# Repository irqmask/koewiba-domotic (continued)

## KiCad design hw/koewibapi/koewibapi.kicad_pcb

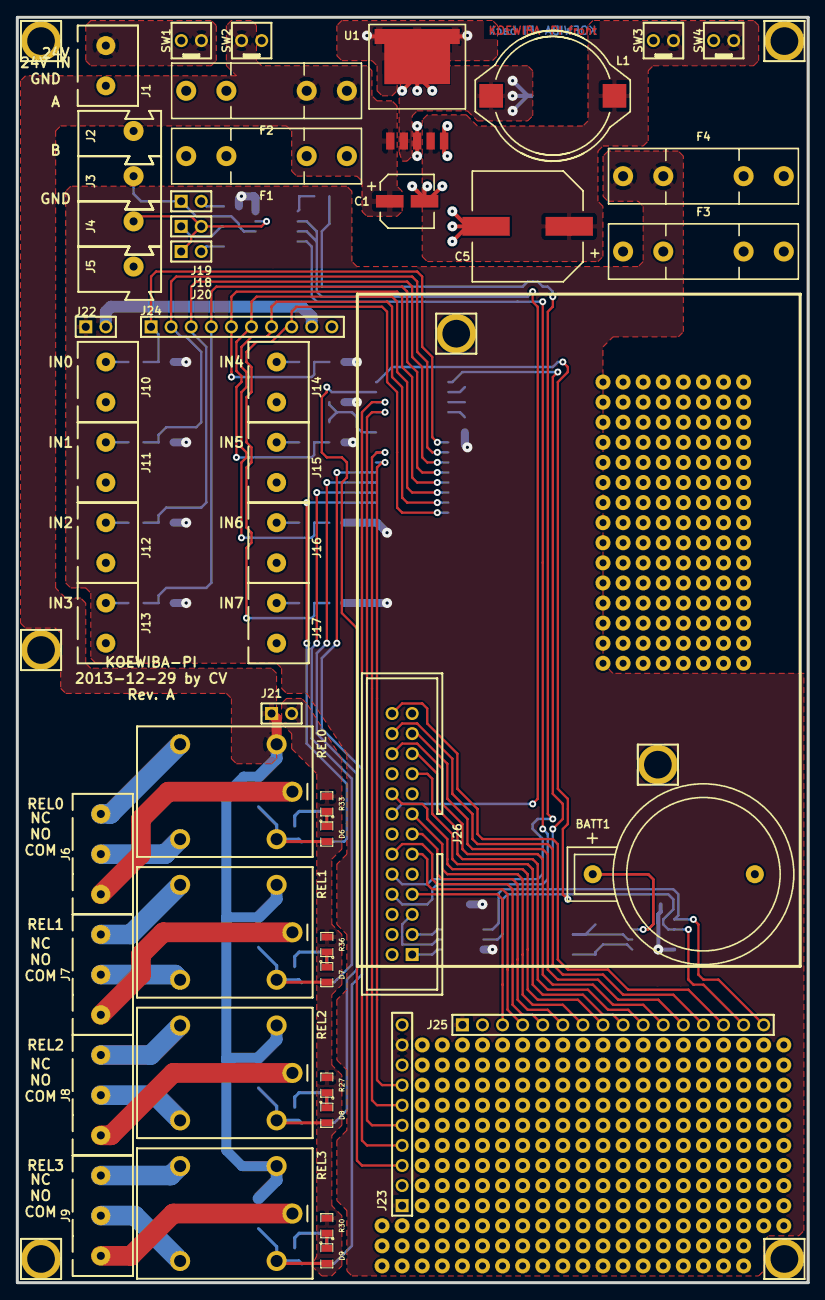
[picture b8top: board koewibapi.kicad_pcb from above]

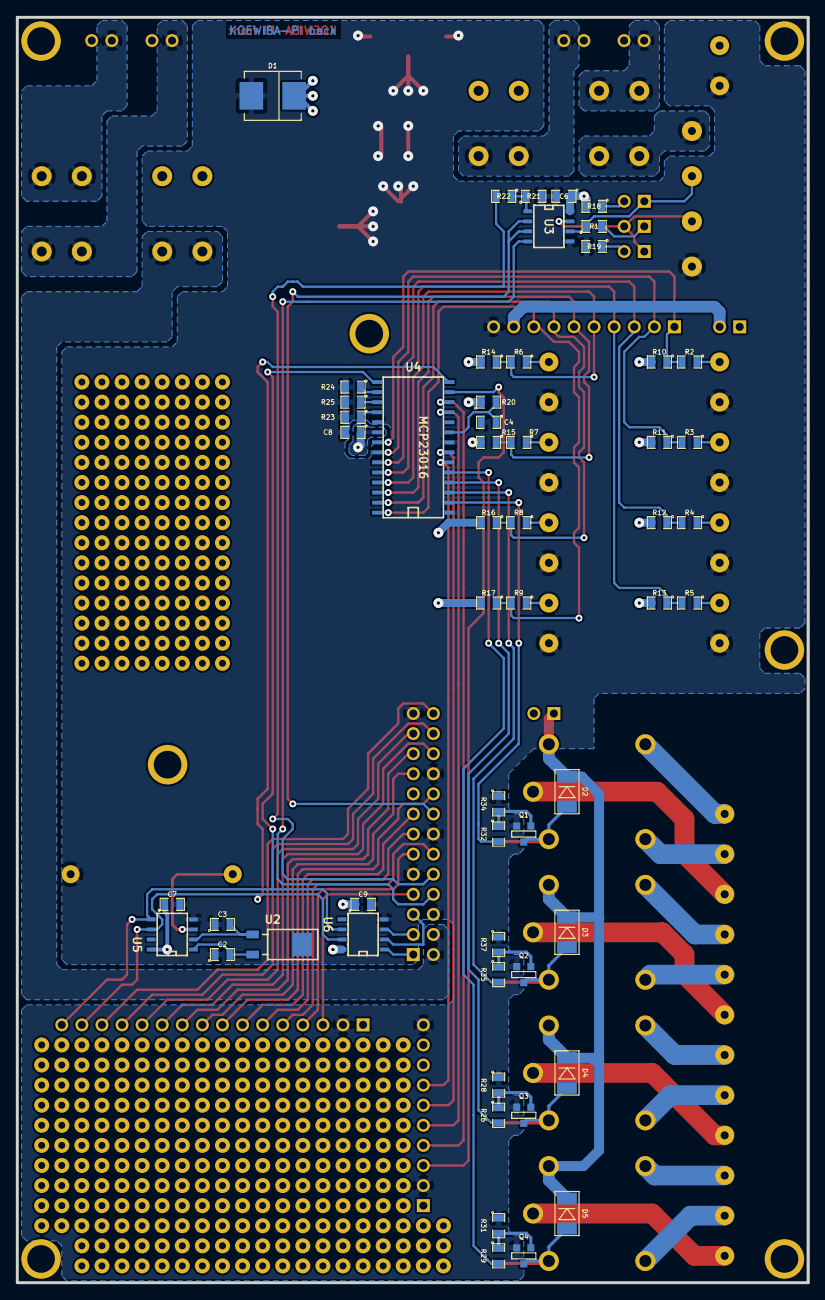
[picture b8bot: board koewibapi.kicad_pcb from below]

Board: 2 copper layers, 100.0 x 160.0 mm, 134 parts (54 on the bottom side), 96 nets.

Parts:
BATT1: 3V; CR2032H
C1: 100uF; cp_smd_6.3
C2, C3: 12.5pF; SM0805
C4: 33pF; SM0805
C5: 1000uF; cp_smd_12.5
C6, C7, C8, C9: 100nF; SM0805
D1: B_340_F; SMC
D2, D3, D4, D5: 1N4148; MINIMELF
D6, D7, D8, D9: LED_2,2V_25mA; SM0805
F1: 250V/1A_T; FUSE5-20
F2: 250V2,5A_T; FUSE5-20
F3: 250V/1,5A_T; FUSE5-20
F4: 250V/250mA_T; FUSE5-20
FIELD2x1, FIELD2x1#2, FIELD2x1#3, FIELD2x1#4, FIELD2x1#5: VAL**; FIELD2x1
FIELD5x2, FIELD5x2#2, FIELD5x2#3: VAL**; FIELD5x2
FIELD5x3, FIELD5x3#2, FIELD5x3#3: VAL**; FIELD5x3
FIELD5x4, FIELD5x4#2: VAL**; FIELD5x4
FIELD5x5, FIELD5x5#2, FIELD5x5#3, FIELD5x5#4, FIELD5x5#5, FIELD5x5#6, FIELD5x5#7, FIELD5x5#8, FIELD5x5#9: VAL**; FIELD5x5
H1, H2, H3, H4, H5, H6, H7: HOLE; HOLE_3.5mm
J1: POWER_IN_24V; CLAMP_5,08mm_2pole_stackable
J2: BUS_24V; WAGO243
J3, J4: CONN_1X1; WAGO243
J5: BUS_GND; WAGO243
J6: REL0; CLAMP_5,08mm_3pole_stackable
J7: REL1; CLAMP_5,08mm_3pole_stackable
J8: REL2; CLAMP_5,08mm_3pole_stackable
J9: REL3; CLAMP_5,08mm_3pole_stackable
J10: IN0; CLAMP_5,08mm_2pole_stackable
J11: IN1; CLAMP_5,08mm_2pole_stackable
J12: IN2; CLAMP_5,08mm_2pole_stackable
J13: IN3; CLAMP_5,08mm_2pole_stackable
J14: IN4; CLAMP_5,08mm_2pole_stackable
J15: IN5; CLAMP_5,08mm_2pole_stackable
J16: IN6; CLAMP_5,08mm_2pole_stackable
J17: IN7; CLAMP_5,08mm_2pole_stackable
J18: Terminate_Bus; HEADER_2x1
J19: Bus_Pull-Up; HEADER_2x1
J20: Bus_Pull-Down; HEADER_2x1
J21: Activate_output_LEDs; HEADER_2x1
J22: Activate_Input_LEDs; HEADER_2x1
J23: unused_GPIO_Pins; HEADER_10x1
J24: Input_Signals; HEADER_10x1
J25: unused_RPi_Rins; HEADER_16x1
J26: CONN_RASPI_REV2; HEADER_26
L1: 220uH; PISR
Q1, Q2, Q3, Q4: BSS138; SOT23-3
R1: 120; SM0805
R2, R3, R4, R5, R6, R7, R8, R9, R18, R19, R23, R24, R25, R27, R30, R33, R36: 1k; SM0805
R10, R11, R12, R13, R14, R15, R16, R17, R21, R28, R31, R34, R37: 10k; SM0805
R20: 3,9k; SM0805
R22: 5k6; SM0805
R26, R29, R32, R35: 100; SM0805
REL0, REL1, REL2, REL3: OMRON_G5LE-1; omron_G5LE-1
SW1: MAIN; PCB_CON2
SW2: 24V_BUS; PCB_CON2
SW3: 5V_RASPI; PCB_CON2
SW4: 5V_LOGIC; PCB_CON2
U1: LM2576; TO263_5
U2: 32.768kHz; CRYSTAL_MS1V-7
U3: MAX487; SO8E
U4: MCP23016; SO28
U5: DS1307; SO8E
U6: PCA9517; SO8E

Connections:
+3.3V: J26.1, U6.1
+5V: C6.1, C7.1, C8.1, C9.1, F4.2, J22.1, J23.1, J23.9, J25.1, R10.2, R11.2, R12.2, R13.2, R14.2, R15.2, R16.2, R17.2, R18.2, R20.1, U3.8, U4.20, U5.8, U6.8
+24V: C1.1, D2.2, D3.2, D4.2, D5.2, F2.2, J21.1, REL0.5, REL1.5, REL2.5, REL3.5, SW2.2, U1.1
/GP1.4: J23.6, U4.7
/GP1.5: J23.5, U4.11
/GP1.6: J23.4, U4.12
/GP1.7: J23.3, U4.13
/GPINT: J23.7, U4.6
/IN0: J24.1, R2.2, R10.1, U4.21
/IN1: J24.2, R3.2, R11.1, U4.22
/IN2: J24.3, R4.2, R12.1, U4.23
/IN3: J24.4, R5.2, R13.1, U4.24
/IN4: J24.5, R6.2, R14.1, U4.25
/IN5: J24.6, R7.2, R15.1, U4.26
/IN6: J24.7, R8.2, R16.1, U4.27
/IN7: J24.8, R9.2, R17.1, U4.28
/RGPIO4: J25.3, J26.7
/RGPIO7: J25.14, J26.26
/RGPIO8: J25.13, J26.24
/RGPIO9: J25.10, J26.21
/RGPIO10: J25.9, J26.19
/RGPIO11: J25.12, J26.23
/RGPIO17: J25.4, J26.11
/RGPIO18: J25.5, J26.12
/RGPIO22: J25.7, J26.15
/RGPIO24: J25.8, J26.18
/RGPIO25: J25.11, J26.22
/RGPIO27: J25.6, J26.13
/RSCL: J26.5, U6.2
/RSDA: J26.3, U6.3
/RXD: J26.10, R22.2
/Relays_0-1/LEDVCC: J21.2, R27.2, R30.2, R33.2, R36.2
/Relays_0-1/OUTCOM1: J6.3, REL0.1
/Relays_0-1/OUTCOM2: J7.3, REL1.1
/Relays_0-1/OUTNC1: J6.1, REL0.4
/Relays_0-1/OUTNC2: J7.1, REL1.4
/Relays_0-1/OUTNO1: J6.2, REL0.3
/Relays_0-1/OUTNO2: J7.2, REL1.3
/Relays_0-1/REL1: R32.2, U4.2
/Relays_0-1/REL2: R35.2, U4.3
/Relays_2-3/OUTCOM1: J8.3, REL2.1
/Relays_2-3/OUTCOM2: J9.3, REL3.1
/Relays_2-3/OUTNC1: J8.1, REL2.4
/Relays_2-3/OUTNC2: J9.1, REL3.4
/Relays_2-3/OUTNO1: J8.2, REL2.3
/Relays_2-3/OUTNO2: J9.2, REL3.3
/Relays_2-3/REL1: R26.2, U4.4
/Relays_2-3/REL2: R29.2, U4.5
/SCL: J25.15, U4.14, U5.6, U6.7
/SDA: J25.16, U4.15, U5.5, U6.6
/TXD: J26.8, U3.4
/TXDEN: J26.16, U3.2, U3.3
GND: BATT1.2, C1.2, C2.1, C3.1, C4.2, C5.2, C6.2, C7.2, C8.2, C9.2, D1.1, J1.2, J5.1, J10.2, J11.2, J12.2, J13.2, J14.2, J15.2, J16.2, J17.2, J23.2, J23.10, J24.10, J25.2, J26.6, J26.9, J26.14, J26.20, J26.25, Q1.2, Q2.2, Q3.2, Q4.2, R19.2, R21.2, R23.2, R24.2, R25.2, R28.1, R31.1, R34.1, R37.1, U1.3, U1.5, U3.5, U4.1, U4.8, U4.19, U5.4, U6.4
unnamed: J11.1, R3.1
unnamed: J10.1, R2.1
unnamed: J15.1, R7.1
unnamed: J14.1, R6.1
unnamed: J16.1, R8.1
unnamed: J17.1, R9.1
unnamed: J13.1, R5.1
unnamed: J12.1, R4.1
unnamed: J20.2, R19.1
unnamed: J19.2, R18.1
unnamed: J18.1, R1.2
unnamed: R24.1, U4.16
unnamed: R25.1, U4.17
unnamed: R23.1, U4.18
unnamed: R21.1, R22.1, U3.1
unnamed: D1.2, L1.1, U1.2
unnamed: F4.1, SW4.2
unnamed: F3.1, SW3.2
unnamed: F1.2, SW2.1
unnamed: J1.1, SW1.1
unnamed: F1.1, J2.1
unnamed: F2.1, SW1.2
unnamed: BATT1.1, U5.3
unnamed: C2.2, U2.1, U5.1
unnamed: C3.2, U2.2, U5.2
unnamed: F3.2, J26.2, J26.4
unnamed: C5.1, L1.2, SW3.1, SW4.1, U1.4
unnamed: J3.1, J19.1, R1.1, U3.6
unnamed: J4.1, J18.2, J20.1, U3.7
unnamed: C4.1, R20.2, U4.9
unnamed: J22.2, J24.9
unnamed: D2.1, D6.2, Q1.3, REL0.2
unnamed: D7.1, R36.1
unnamed: D3.1, D7.2, Q2.3, REL1.2
unnamed: D6.1, R33.1
unnamed: Q2.1, R35.1, R37.2
unnamed: Q1.1, R32.1, R34.2
unnamed: D9.1, R30.1
unnamed: D4.1, D8.2, Q3.3, REL2.2
unnamed: D5.1, D9.2, Q4.3, REL3.2
unnamed: D8.1, R27.1
unnamed: Q4.1, R29.1, R31.2
unnamed: Q3.1, R26.1, R28.2

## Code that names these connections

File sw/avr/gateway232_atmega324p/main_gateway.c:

/**
 * @addtogroup BUS_GATEWAY
 *
 * @{
 * @file    main_gateway.c
 * @brief   Main entry point of bus gateway. 
 *          It translates bus messages to serial messages and vice-versa.
 *          Additionally 4 inputs which a connected to pi2-base PCB are 
 *          monitored.
 * @author  Christian Verhalen
 *///---------------------------------------------------------------------------
/*
 * Copyright (C) 2021  christian <irqmask@web.de>
 *
 * This program is free software: you can redistribute it and/or modify
 * it under the terms of the GNU General Public License as published by
 * the Free Software Foundation, either version 3 of the License, or
 * (at your option) any later version.
 *
 * This program is distributed in the hope that it will be useful,
 * but WITHOUT ANY WARRANTY; without even the implied warranty of
 * MERCHANTABILITY or FITNESS FOR A PARTICULAR PURPOSE.  See the
 * GNU General Public License for more details.
 *
 * You should have received a copy of the GNU General Public License
 * along with this program.  If not, see <http://www.gnu.org/licenses/>.
 */
// --- Include section ---------------------------------------------------------

#include <avr/io.h>
#include <avr/interrupt.h>
#include <avr/pgmspace.h>
#include <avr/wdt.h>

#include "appconfig.h"
#include "bus.h"
#include "bus_gateway.h"
#include "cmddef_common.h"
#include "moddef_common.h"
#include "pcbconfig.h"
#include "input.h"
#include "register.h"
#include "serialcomm.h"
#include "sleepmode.h"
#include "timer.h"

#ifndef NO_BLOCK_MESSAGE
 #include "block_message.h"
#endif
#ifndef NO_EEPROM_SPI
 #include "eeprom_spi.h"
#endif

// TODO remove after debug
#include "led_debug.h"

// --- Definitions -------------------------------------------------------------

// --- Type definitions --------------------------------------------------------

// --- Local variables ---------------------------------------------------------

static timer_data_t g_LED_timer;
static timer_data_t g_input_timer;

// --- Global variables --------------------------------------------------------

extern const unsigned char app_versioninfo[];

sBus_t              g_bus;
serial_msg_t        g_serial;
scomm_phy_t         *g_serphy = &g_serial.serphy;

// --- Module global variables -------------------------------------------------

// --- Local functions ---------------------------------------------------------

ISR(PCINT0_vect)
{
    // nothing to do here, but ISR is needed for sleep-mode
}

ISR(PCINT1_vect)
{
    // nothing to do here, but ISR is needed for sleep-mode
}

ISR(PCINT2_vect)
{
    // nothing to do here, but ISR is needed for sleep-mode
}

ISR(PCINT3_vect)
{
    // nothing to do here, but ISR is needed for sleep-mode
}

static void io_initialize(void)
{
    DDRA  |= ((0<<DDA7) | (0<<DDA6) | (0<<DDA5) | (0<<DDA4) | (0<<DDA3) | (0<<DDA2) | (0<<DDA1) | (0<<DDA0) );
    PORTA |= ((0<<PA7)  |  (0<<PA6)  |  (0<<PA5)  |  (0<<PA4)  |  (1<<PA3)  |  (1<<PA2)  |  (1<<PA1)  |  (1<<PA0)  );
    PCMSK0 |= ((1<<PCINT3) | (1<<PCINT2) | (1<<PCINT1) | (1<<PCINT0)); // activate pin-change-interrupts for the inputs

    DDRB  |= ((1<<DDB7) | (0<<DDB6) | (0<<DDB5) | (0<<DDB4) | (0<<DDB3) | (0<<DDB2) | (1<<DDB1) | (1<<DDB0) );
    PORTB |= ((0<<PB7)   |  (0<<PB6)  |  (0<<PB5)  |  (0<<PB4)  |  (0<<PB3)  |  (0<<PB2)  |  (0<<PB1)  |  (0<<PB0)  );

    DDRC  |= ((0<<DDC7) | (0<<DDC6) | (1<<DDC5) | (0<<DDC4) | (0<<DDC3) | (0<<DDC2) | (0<<DDC1) | (0<<DDC0) );
    PORTC |= ((0<<PC7)   |  (0<<PC6)  |  (0<<PC5)  |  (0<<PC4)  |  (0<<PC3)  |  (0<<PC2)  |  (0<<PC1)  |  (0<<PC0)  );

    DDRD  |= ((0<<DDD7) | (0<<DDD6) | (1<<DDD5) | (1<<DDD4) | (0<<DDD3) | (0<<DDD2) | (0<<DDD1) | (0<<DDD0) );
    PORTD |= ((0<<PD7)   |  (0<<PD6)  |  (0<<PD5)  |  (0<<PD4)  |  (0<<PD3)  |  (0<<PD2)  |  (0<<PD1)  |  (0<<PD0)  );
}

/// send the version information
static inline void answer_version_info_request (uint16_t sender)
{
    uint8_t msg[MOD_VERSIONINFO_LEN + 1], i;

    msg[0] = eCMD_STATE_VERSION;
    for (i=0; i<MOD_VERSIONINFO_LEN; i++) {
        msg[i + 1] = pgm_read_byte(&app_versioninfo[i]);
    }
    bus_send_message(&g_bus, sender, sizeof(msg), msg);
}

static inline void interpret_message (uint16_t sender, uint8_t msglen, uint8_t* msg)
{
    switch (msg[0]) {
    case eCMD_REQUEST_REG:
        // fall through
    case eCMD_SET_REG_8BIT:
        // fall through
    case eCMD_SET_REG_16BIT:
        // fall through
    case eCMD_SET_REG_32BIT:
        register_do_command(sender, msglen, msg);
        break;

    case eCMD_REQUEST_INFO_OF_TYPE:
        if (msglen == 2 && msg[1] == eINFO_VERSION) {
            answer_version_info_request(sender);
        }
        break;

#ifndef NO_BLOCK_MESSAGE
    case eCMD_BLOCK_START:
        block_message_start(sender, msglen, msg);
        break;
    case eCMD_BLOCK_DATA:
        block_message_data (sender, msglen, msg);
        break;
    case eCMD_BLOCK_END:
        block_message_end  (sender, msglen, msg);
        //no break
    case eCMD_BLOCK_RESET:
        block_data_reset();
        break;
#endif

    case eCMD_SLEEP:
        bus_sleep(&g_bus);
        break;

    case eCMD_RESET:
        cli();
        wdt_enable(WDTO_15MS);
        while (1); // wait until watch-dog resets the controller.
        break;

    default:
        break;
    }
}

static void send_input_state(uint8_t input, uint8_t value)
{
    uint8_t cmd[3];
    cmd[0] = eCMD_STATE_8BIT;
    cmd[1] = APP_eReg_Input1 + input;
    cmd[2] = value;

    bus_send_message(&g_bus, g_bus.sCfg.uOwnAddress & BUS_SEGBRDCSTMASK, sizeof(cmd), cmd);
    serial_send_message(&g_serial.serphy, g_bus.sCfg.uOwnAddress, BUS_BRDCSTADR, sizeof(cmd), cmd);
}

static void check_inputs(void)
{
    uint8_t opened = input_went_high();
    uint8_t closed = input_went_low();

    for (uint8_t i=0; i<INPUT_NUM_PINS; i++) {
        if ((closed & (1<<i)) != 0) {
            send_input_state(i, 0);
        }
        else if ((opened & (1<<i)) != 0) {
            send_input_state(i, 1);
        }
    }
}

// --- Module global functions -------------------------------------------------

// --- Global functions --------------------------------------------------------

int main(void)
{
    uint8_t msglen = 0;
    uint8_t msg[BUS_MAXRECVMSGLEN];
    uint16_t sender = 0;
    uint16_t module_id = 0;

    io_initialize();
    input_initialize();
    timer_initialize();
    bgw_initialize(&g_serial);

    //register_set_u16(MOD_eReg_ModuleID, 0x0003);
    register_get(MOD_eReg_ModuleID, 0, &module_id);
    bus_configure(&g_bus, module_id);
    bus_initialize(&g_bus, 0);// initialize bus on UART 0

    sei();
    LED_STATUS_OFF;
    LED_ERROR_OFF;

    timer_start(&g_LED_timer, TIMER_MS_2_TICKS(1000));
    timer_start(&g_input_timer, TIMER_MS_2_TICKS(20));

    while (1) {
        // check for message and read it
        if (bus_get_message(&g_bus)) {
            if (bgw_forward_bus_msg(&g_bus, &g_serial, &sender, &msglen, msg)) {
                interpret_message(sender, msglen, msg);
            }
        }
        if (bgw_get_serial_msg(&g_serial)) {
            if (bgw_forward_serial_msg(&g_bus, &g_serial, &sender, &msglen, msg)) {
                interpret_message(sender, msglen, msg);
            }
        }

        if (timer_is_elapsed(&g_input_timer)) {
            timer_start(&g_input_timer, TIMER_MS_2_TICKS(20));
            input_background();
            check_inputs();
        }

        if (timer_is_elapsed(&g_LED_timer)) {
            // cyclic reset of error LED
            LED_ERROR_OFF;
            LED_STATUS_TOGGLE;
            timer_start(&g_LED_timer, TIMER_MS_2_TICKS(1000));
        }

        if (sleep_check_and_goodnight() == true) {
            // bus gone to sleep and is now woken up
            // wait for first pending byte, then set module to running state
            g_bus.eState = eBus_InitWait;
            sleep_request(false);
        }
    }
    return 0;
}

/** @} */

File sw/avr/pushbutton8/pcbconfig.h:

/**
 * @addtogroup TASTER8_PCBCONFIG
 * @brief PCB configuration of the taster8 application.
 *
 * @{
 * @file    pcbconfig.h
 * @brief   PCB configuration of the taster8 application.
 *
 * @author  Christian Verhalen
 *///---------------------------------------------------------------------------
#ifndef _PCBCONFIG_H_
#define _PCBCONFIG_H_

// --- Include section ---------------------------------------------------------

#include "prjtypes.h"

// --- Definitions -------------------------------------------------------------

#define BUS_PCBCONFIG 1
#define BUS_DDR_ENASND0     DDRD
#define BUS_PORT_ENASND0    PORTD
#define BUS_ENASND0         PD2

#define LATCH_OE_ENABLED    1

#define SPI_PCBCONFIG  1
//! Defines the DDR of a port which contains the MOSI signal.
#define SPI_DDR_MOSI   DDRB
//! Defines the DDR of a port which contains the MISO signal.
#define SPI_DDR_MISO   DDRB
//! Defines the DDR of a port which contains the SCK signal.
#define SPI_DDR_SCK    DDRB
//! Defines the DDR of a port which contains the standard slave select signal.
#define SPI_DDR_SS     DDRB
//! Defines the PORT which contains the standard slave select signal.
#define SPI_PORT_SS    PORTB
//! Defines the MOSI pin.
#define SPI_MOSI       PB3
//! Defines the MISO pin.
#define SPI_MISO       PB4
//! Defines the SCK pin.
#define SPI_SCK        PB5
//! Defines the SS (slave select) pin.
#define SPI_SS         PB2

// switch inputs
#define INPUT_PCBCONFIG     1
#define INPUT_NUM_PINS      8
#define INPUT_PORT_0        PORTD
#define INPUT_PIN_0         PIND
#define INPUT_DDR_0         DDRD
#define INPUT_0             PD3
#define INPUT_PORT_1        PORTC
#define INPUT_PIN_1         PINC
#define INPUT_DDR_1         DDRC
#define INPUT_1             PC4
#define INPUT_PORT_2        PORTC
#define INPUT_PIN_2         PINC
#define INPUT_DDR_2         DDRC
#define INPUT_2             PC2
#define INPUT_PORT_3        PORTC
#define INPUT_PIN_3         PINC
#define INPUT_DDR_3         DDRC
#define INPUT_3             PC0
#define INPUT_PORT_4        PORTD
#define INPUT_PIN_4         PIND
#define INPUT_DDR_4         DDRD
#define INPUT_4             PD4
#define INPUT_PORT_5        PORTC
#define INPUT_PIN_5         PINC
#define INPUT_DDR_5         DDRC
#define INPUT_5             PC5
#define INPUT_PORT_6        PORTC
#define INPUT_PIN_6         PINC
#define INPUT_DDR_6         DDRC
#define INPUT_6             PC3
#define INPUT_PORT_7        PORTC
#define INPUT_PIN_7         PINC
#define INPUT_DDR_7         DDRC
#define INPUT_7             PC1


// Pin assignments of board keys and LEDs
#define LEDSKEYS_PCBCONFIG  1
#define KEY0_DDR            DDRD
#define KEY0_PORT           PORTD
#define KEY0_IPORT          PIND
#define KEY0_PIN            PD3
#define KEY1_DDR            DDRC
#define KEY1_PORT           PORTC
#define KEY1_IPORT          PINC
#define KEY1_PIN            PC4
#define KEY2_DDR            DDRC
#define KEY2_PORT           PORTC
#define KEY2_IPORT          PINC
#define KEY2_PIN            PC2
#define KEY3_DDR            DDRC
#define KEY3_PORT           PORTC
#define KEY3_IPORT          PINC
#define KEY3_PIN            PC0
#define KEY4_DDR            DDRD
#define KEY4_PORT           PORTD
#define KEY4_IPORT          PIND
#define KEY4_PIN            PD4
#define KEY5_DDR            DDRC
#define KEY5_PORT           PORTC
#define KEY5_IPORT          PINC
#define KEY5_PIN            PC5
#define KEY6_DDR            DDRC
#define KEY6_PORT           PORTC
#define KEY6_IPORT          PINC
#define KEY6_PIN            PC3
#define KEY7_DDR            DDRC
#define KEY7_PORT           PORTC
#define KEY7_IPORT          PINC
#define KEY7_PIN            PC1

#define KEY0_WAKEUP         PCINT19 // PD3
#define KEY0_WAKEUP_REG     PCMSK2
#define KEY1_WAKEUP         PCINT12 // PC4
#define KEY1_WAKEUP_REG     PCMSK1
#define KEY2_WAKEUP         PCINT10 // PC2
#define KEY2_WAKEUP_REG     PCMSK1
#define KEY3_WAKEUP         PCINT8  // PC0
#define KEY3_WAKEUP_REG     PCMSK1
#define KEY4_WAKEUP         PCINT20 // PD4
#define KEY4_WAKEUP_REG     PCMSK2
#define KEY5_WAKEUP         PCINT13 // PC5
#define KEY5_WAKEUP_REG     PCMSK1
#define KEY6_WAKEUP         PCINT11 // PC3
#define KEY6_WAKEUP_REG     PCMSK1
#define KEY7_WAKEUP         PCINT9  // PC1
#define KEY7_WAKEUP_REG     PCMSK1

#define SN74595_REG_BYTES	1		// Number of bytes to send in full spi message
#define LATCH_OE_ENABLED

#define LED_OE_DDR          DDRD
#define LED_OE_PORT         PORTD
#define LED_OE_PIN          PD6
#define LED_STB_DDR         DDRD
#define LED_STB_PORT        PORTD
#define LED_STB_PIN         PD5
#define LED0                6
#define LED1                5
#define LED2                0
#define LED3                4
#define LED4                7
#define LED5                3
#define LED6                2
#define LED7                1

// --- Type definitions --------------------------------------------------------

// --- Local variables ---------------------------------------------------------

// --- Global variables --------------------------------------------------------

// --- Module global variables -------------------------------------------------

// --- Local functions ---------------------------------------------------------

// --- Module global functions -------------------------------------------------

// --- Global functions --------------------------------------------------------

#endif // _PCBCONFIG_H_
/** @} */

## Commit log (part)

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2020-01-26 ioloop: fix timer rollover bug kwbmqttgateway: re-connect when connection lost added API documentation
2020-01-26 fixed kwbrouter option parsing
2020-02-17 Improve logging of connections
    * use address and port of remote for connection name
    * removed unused constructors
    * removed duplicate message logging
2020-02-17 debug logging
2020-02-24 Router uses RouteConnection* as reference
2020-03-02 Improve message logging
2020-03-14 * Move os/shared into libkwb * Add googletest * Change CUnit tests into googletest tests * mqttgateway: do not retain messages
2020-03-19 Forward messages to gateway also over serial again
2020-03-27 General cleanup
2020-04-30 Add forgotten linker script for gateway
2020-05-05 Add hardware doc drafts and sw drawings
2020-05-15 Allow commandline argument -o and -n beeing also hexadecimal
    -o own node address
    -n node address
2020-10-10 Fix typo, add licenses
2020-10-10 Use libkwb's connection classes instead of routeconnection
2020-10-13 kwbconfiguration uses libkwb connection classes
    kwbconfiguration is now able to connect to a kwbrouter to communicate
2020-10-15 Add missing script
2020-10-21 Document code and APIs, Fix doxygen warnings
    The components include, kwbrouter, libkwb, libsystem, kwbtest and
    unittests have been documented.
2020-10-23 Further document functions, types and variables
    * kwbconfiguration (partly)
2021-03-03 Moved connectors towards inner board to avoid TH pads touching housing
2021-03-03 added testpoints and LEDs updated 3d footprints
2021-03-03 Added LED and testpoints
2021-03-03 Increase hole diameter of WAGO243 connectors by 0.1mm
2021-03-03 add switch5 register layout
2021-03-03 Add input module Set outputs according to input and input mode
2021-03-10 moved relay switching into new output module
    add license texts
    implement first register setter/getter
2021-03-20 Implemet alarm timer to switch on/off
2021-03-31 Update documentation
2021-03-31 Fix: Add missing cache library
2021-03-31 Added 3d images Added component placement drawings Added gerber files Fixes rescue library mess
2021-03-31 Add calculation documentation for zagwire protocol.
2021-03-31 Initial version of blindcontrol for 5 blinds
2021-03-31 preserved revision A schematic
2021-03-31 initial version of pushbutton8 hw and sw
2021-04-01 Add eclipse project files for pushbutton8
2021-04-02 Add initial revision blindcontrol for 5 motors controlled over sn74595
2021-04-02 Add debug LEDs for scheduler. Currentlty not working! Stray bytes!
2021-04-03 Add blind-control_5x and test_motor_switch_5 to buildall script Set correct versions for blind-control_5x and test_motor_switch_5
2021-04-07 Fix missing doxygen documentation
2021-04-30 Fix mixed up/down keys in blindcontrol
2021-06-19 Fix crash on startup. Pause router for 2 seconds if message failed to send
2021-06-20 limit list size of sent messages
2021-06-20 Fix setting day of week.
2021-07-04 Prevent gateway from going into sleep
2021-07-23 Send current intensity if led finishes changing
2021-12-20 Added some notices for getting kwbmonitor and kwbmqttgateway installed.
2021-12-20 elektor_bus_node: get bus segment from own address and merge with target address
2021-12-20 Intermediate status with fixed message table to send the correct message when a key is pressed.
2021-12-20 add functions to draw temperature
2021-12-20 dim display after 10s, switch off after 60s
2021-12-20 switch up/down buttons
2021-12-20 clear frame error flag if it occurs
2022-01-28 Add initial heatervalve schematics and pin assignment (work in progress)
2022-04-09 Add heatervalve schematic
2022-04-21 add initial application for heatervalve attiny1634 firmware
    * currently no functionality implemented
2022-04-21 remove debug output in motor component
2022-04-21 add command srt to set remotely measures temperatures
2022-04-22 add simple proportional regulation ouput motorposition at end of movement
2022-04-22 add temperature offset to given temperature
2022-04-22 heatervalve stm8: debug messages begin with #
2022-04-22 heatervalve: add register to set kp and forward it to the stm8
2022-06-15 blind-control_5_atmega328p: Update Eclipse project file
2022-10-03 Fix mixup of blindcontrol input keys
2022-10-09 Add motor_switch_3pole pcb component drawings
2022-11-12 generate version file for os seperately
    so no cmake is required for building AVR firmware
2022-11-27 Proper end kwbconfiguration application
2022-11-27 roomthermostate: validate desired temperature value received over bus
2022-12-10 all sourcecode filenames lowercase
2022-12-10 Add basic menu items to backup and restore a module's configuration
    * add menu items
    * prepare basic data structure
2022-12-10 Implement backup of register values of a module
2022-12-10 Implement restoring and verifying register values
2022-12-18 register / backup work in progress
2022-12-18 no logging of communication to console in default mode
2022-12-19 Roomthermostat: Add timer to set temperature at certain times a day
2022-12-19 Update roomthermostate register layout
2023-10-12 update list of required packages
2023-10-13 add better front panel with wall inlets and arced holes
2023-10-13 Update to KiCAD6: bus-module_atmega328
2023-10-14 roomthermostat: Update PCB edged and add ext. sensor
    * add edge.cuts cutouts for mounting screws and frame
    * add external connector for temperature sensor
    (do not add internal and external sensor at the same time!)
2023-10-15 Update to KiCAD6: motor_switch_3pole_5x
2023-10-15 Update to KiCAD6: switch_3pole_5x
2023-10-15 Update to KiCAD6: gateway_usb
2023-10-15 Update to KiCAD6: buscom-hub
2023-11-19 heatervalve_interface: Update schematic and add PCB design
2023-12-06 heatervalve-interface Create gerber files for Rev A
2023-12-06 roomthermostat: add gerber files for Rev C
2023-12-06 bus-module_atmega328: create new gerber files for Rev C
2023-12-18 basic_app_stmega324p: Add missing app_on_pinchangeinterrupt()
    as empty template
2023-12-18 basic_app_attiny1634: Add missing app_on_pinchangeinterrupt()
    as empty template
2023-12-18 heatervalve_gateway_attiny1624: Add missing app_on_pinchangeinterrupt()
2023-12-18 roomthermostat: Add missing app_on_pinchangeinterrupt()
2023-12-18 elektor_bus-node_atmega88: Add missing app_on_pinchangeinterrupt()
2023-12-18 remove old version.h template file
2023-12-28 Correction of the blind-control_5x register numbers.
2023-12-28 debounce inputs of pushbutton8
2023-12-28 pushbutton8: Behavior of application configurable by register settings.
2023-12-29 pushbutton8: Add make targets in Eclipse project
2023-12-29 attiny1634: fix access to ext. SPI EEProm
    * add extra spi_transmit_blk routine for attiny1634
    * do not read SPI data register twice on ATtiny1634! Only first read is valid.
2024-01-04 Update gitignore for sw folder and sub-folders
2024-01-31 atmega328pb: disable related projects in buildscripts
    so it does not generate a ton of errors, if an older libavr is used
2024-01-31 heatervale-interface: Disable UART when block transfer is ongoing
2024-01-31 heatervalve-interface: reserved 0x000A as board id
2024-01-31 scheduler_attiny1634: Cleanup and prepare for firmware-upload
2024-01-31 heatervalve: First iteration of application register layout
2024-01-31 roomthermostat: Switch input module from 'inputs' to 'input'
2024-02-01 remove obsolete inputs module
2024-02-11 heatervalve_interface: enable pull-up resistors for contact inputs
    On ATtiny1634 pull-ups are enabled by writing to register PUExn instead of PORTxn
2024-02-11 use own header instead of STM8 BSP
2024-02-11 heatervale: set uart to 9600bd
2024-02-11 roomthermostat: Dislpay 'SOLL' and 'IST' over associated temperature values
2024-02-11 heatervalve_interface: activate pin-change wake-up for contacts
2024-04-12 blind-control_5: module sn74595 stores the spi message by itself.
    - because different modules should put their bits into the SPI message to 74HC595, the
    data is now stored in a array within the module sn74595.c . Therefore the data must be
    set by calling sn74595_set_byte() before sending the spi message using sn74595_send().
    The set is called with a mask, defining the updated bits.
    - The following modules are affected by the change: pushbutton8, blind-control_5
2025-01-10 Fixed inline functions bug (avr-gcc) by defining it static.
2025-01-11 Split Module and ModuleRegister classes into seperate files
    Furthermore, add unittests for JSON to ModuleRegister conversion.
2025-01-11 Cleanup
2025-01-11 Fix OS build
2025-01-11 Fix versioninfo of elektor_bus-node
2025-01-12 scheduler: Scheduler must not discard received messages
    Previously the scheduler reset the bus when a message has been received, not distinguishing if it was addressed to the scheduler or not.
    Now the scheduler received messages to its address, segment broadcast of same segment and broadcast messages.
2025-01-12 heatervalve: Fix type of putchar()
2025-01-12 roomthermostat: switch on display if new setpoint received
2025-01-12 heatervalve_gateway: add initial register layout file
2025-01-12 heatervalve_gateway: only pull reset to GND. release by setting to high-impedance
2025-01-12 heatervalve_gateway: keep sub-module in reset while updating firmware
2025-01-12 heatervalve: add encoder API
2025-01-12 heatervalve: show '----' in display when started
2025-01-12 heatervalve: Add basic LCD driver
2025-01-12 heatervalve: UART gets receive queue
2025-01-12 heatervalve: remote control STM8 reset from heatervalve_gateway
    - commented code
2025-01-15 Enable SPI to allow EEProm to be programmed
2025-03-10 Update googletest to v1.12.1 to get rid of CMake warning
2025-03-11 Scheduler shall acknowledge also segment broadcast messages
2025-03-18 Remove workaround, preventing gateway going into sleepmode.
    This workaround itself caused issues when a message was received on serial line and should be conveyed to the bus.
2025-04-05 Route message also over serial line, if configured
2025-04-18 kwbconfiguration: Fix crash in MsgBroker
2025-06-21 Fuses.txt: Aligned efuse value to 0xFD.
    Because the upper five bits of the extended fuse are unused they are always read as 1.
2025-06-28 New file 'appregister.md' that describes the application register structure in compareable format.
2025-07-01 Code cleanup
2025-07-06 Use FetchContent to get nlohmann-json and googletest
2025-07-25 Do not install unittest executables
2025-09-23 Fic coverity bugs
2025-11-08 Increase minimum CMake version to 3.16
2025-11-08 Output version on application start
2025-11-08 Added register description "appregister.md" for pushbutton8. JSON layout0009 correction.
2025-11-09 heatervalve: fix warnings
